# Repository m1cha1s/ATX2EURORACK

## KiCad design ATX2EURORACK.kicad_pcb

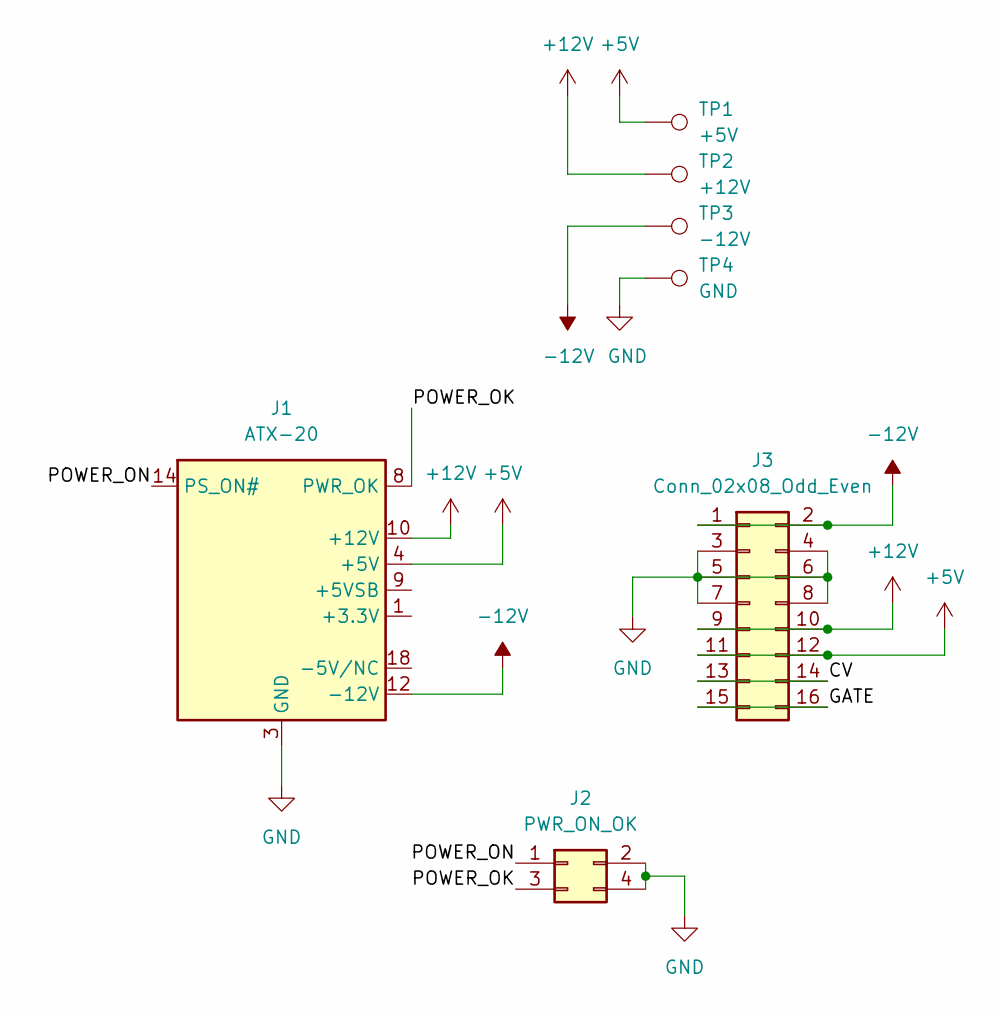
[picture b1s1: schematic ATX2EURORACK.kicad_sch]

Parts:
J1: ATX-20; Molex_Mini-Fit_Jr_5566-20A_2x10_P4.20mm_Vertical
J2: PWR_ON_OK; PinHeader_2x02_P2.54mm_Vertical
J3: Conn_02x08_Odd_Even; IDC-Header_2x08_P2.54mm_Vertical
TP1: +5V; TestPoint_Pad_D4.0mm
TP2: +12V; TestPoint_Pad_D4.0mm
TP3: -12V; TestPoint_Pad_D4.0mm
TP4: GND; TestPoint_Pad_D4.0mm

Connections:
+5V: J1.4 (+5V), J1.6 (+5V), J1.19 (+5V), J1.20 (+5V), J3.11, J3.12, TP1.1
+12V: J1.10 (+12V), J3.9, J3.10, TP2.1
-12V: J1.12 (-12V), J3.1, J3.2, TP3.1
/CV: J3.13, J3.14
/GATE: J3.15, J3.16
/POWER_OK: J1.8 (PWR_OK), J2.3
/POWER_ON: J1.14 (PS_ON#), J2.1
GND: J1.3 (GND), J1.5 (GND), J1.7 (GND), J1.13 (GND), J1.15 (GND), J1.16 (GND), J1.17 (GND), J2.2, J2.4, J3.3, J3.4, J3.5, J3.6, J3.7, J3.8, TP4.1
unnamed: J1.1 (+3.3V), J1.2 (+3.3V), J1.11 (+3.3V)

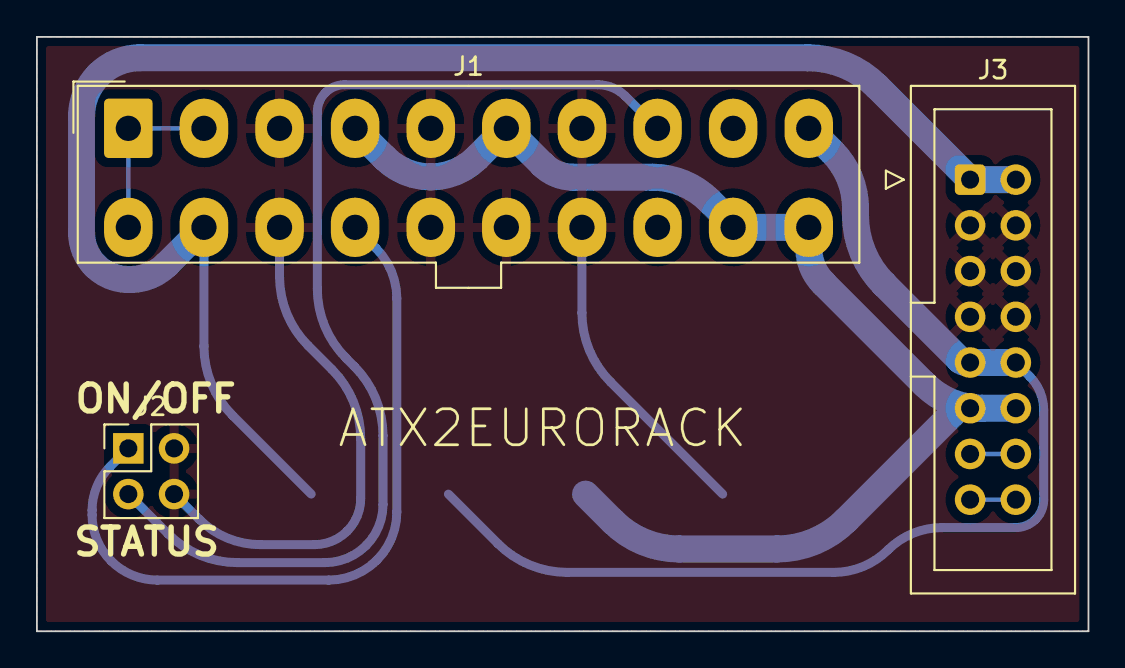
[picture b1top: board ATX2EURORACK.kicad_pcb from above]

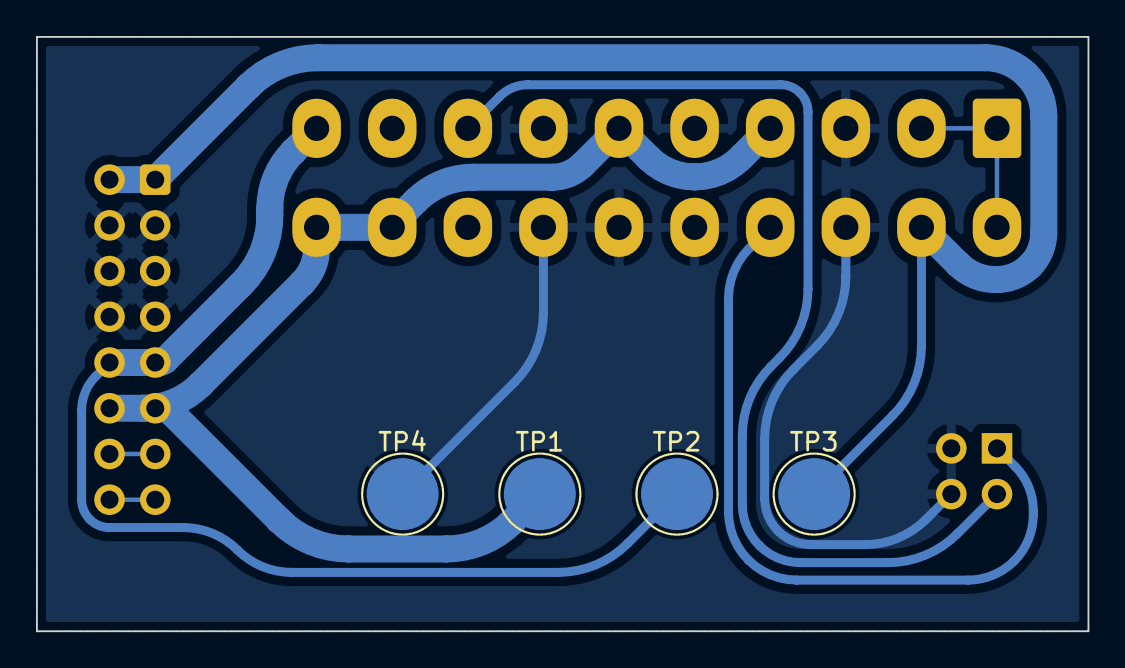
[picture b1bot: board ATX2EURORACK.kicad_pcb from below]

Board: 2 copper layers, 58.4 x 33.0 mm, 7 parts (4 on the bottom side), 9 nets.

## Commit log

2022-10-27 Completed the first(hopefully last) version of this board
2022-10-27 Rounded the tracks
